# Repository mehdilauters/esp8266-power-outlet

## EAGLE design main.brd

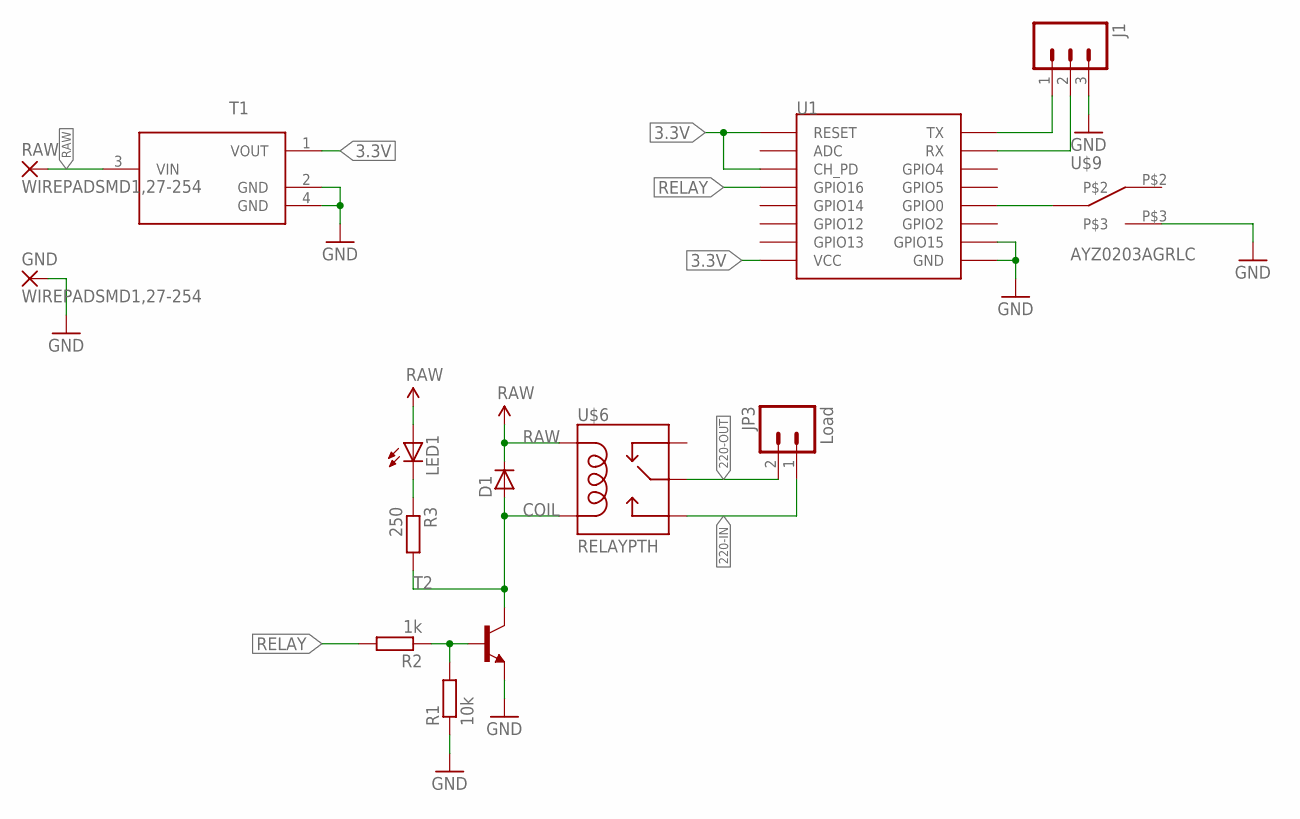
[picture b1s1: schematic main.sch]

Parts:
D1: D-A1-C3; SOT23
GND: WIREPADSMD1,27-254; SMD1,27-2,54
J1: M03PTH; 1X03
JP3: Load; SCREWTERMINAL-5MM-2
LED1: LEDCHIPLED_0603; CHIPLED_0603
R1: 10k; R0603
R2: 1k; R0603
R3: 250; R0603
RAW: WIREPADSMD1,27-254; SMD1,27-2,54
T1: L78L33ACUTR; SOT150P400X160-4N
T2: BC808-NPN-SOT23-BEC; SOT23-BEC
U1: ESP12SMD; ESP12-SMD
U$6: RELAYPTH; RELAY-G5Q
U$9: AYZ0203AGRLC

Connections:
3.3V: T1.1 (VOUT), U1.CH_PD, U1.RESET, U1.VCC
220-IN: JP3.1, U$6.3 (NO)
220-OUT: JP3.2, U$6.2 (MAIN)
COIL: D1.1 (A), R3.2, T2.C, U$6.1 (COIL2)
GND: GND.1, J1.3, R1.1, T1.2 (GND), T1.4 (GND), T2.E, U1.GND, U1.GPIO15, U$9.P$3
unnamed: LED1.C, R3.1
unnamed: U1.GPIO0, U$9.P$1 (COM)
unnamed: R1.2, R2.1, T2.B
RAW: D1.3 (C), LED1.A, RAW.1, T1.3 (VIN), U$6.5 (COIL1)
RELAY: R2.2, U1.GPIO16
RX: J1.2, U1.RXD0 (RX)
TX: J1.1, U1.TXD0 (TX)

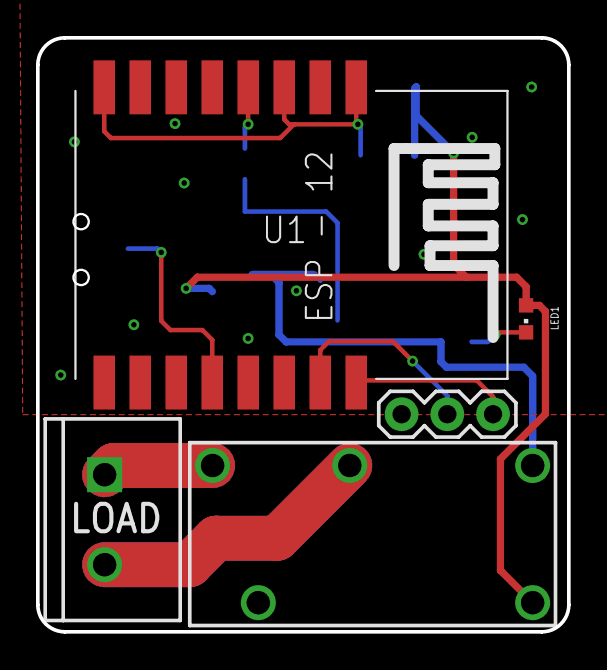
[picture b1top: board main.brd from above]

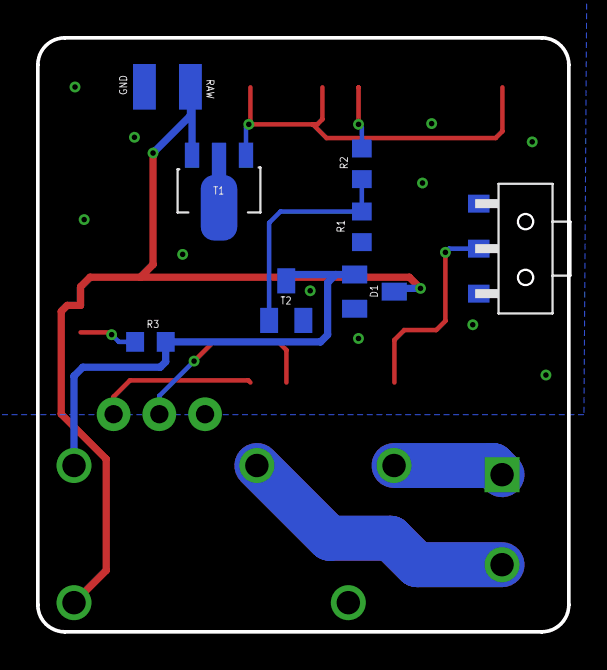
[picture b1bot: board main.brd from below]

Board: 2 copper layers, 29.5 x 33.0 mm, 14 parts (9 on the bottom side), 12 nets.

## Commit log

2016-11-07 Tibzor fixes
2016-11-08 Swapped IN and OUT on silkscreen. REV0 : gerber added (into production).
2017-01-13 Basic working code
2017-01-14 INTERNAL webserver power switch
2017-01-14 TIMEOUT: implementation
2017-01-14 PING: ping implementation (socket connect issue)

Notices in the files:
parts and their libraries:
SparkFun-Connectors: Licensing: Creative Commons ShareAlike 4.0 International - https://creativecommons.org/licenses/by-sa/4.0
